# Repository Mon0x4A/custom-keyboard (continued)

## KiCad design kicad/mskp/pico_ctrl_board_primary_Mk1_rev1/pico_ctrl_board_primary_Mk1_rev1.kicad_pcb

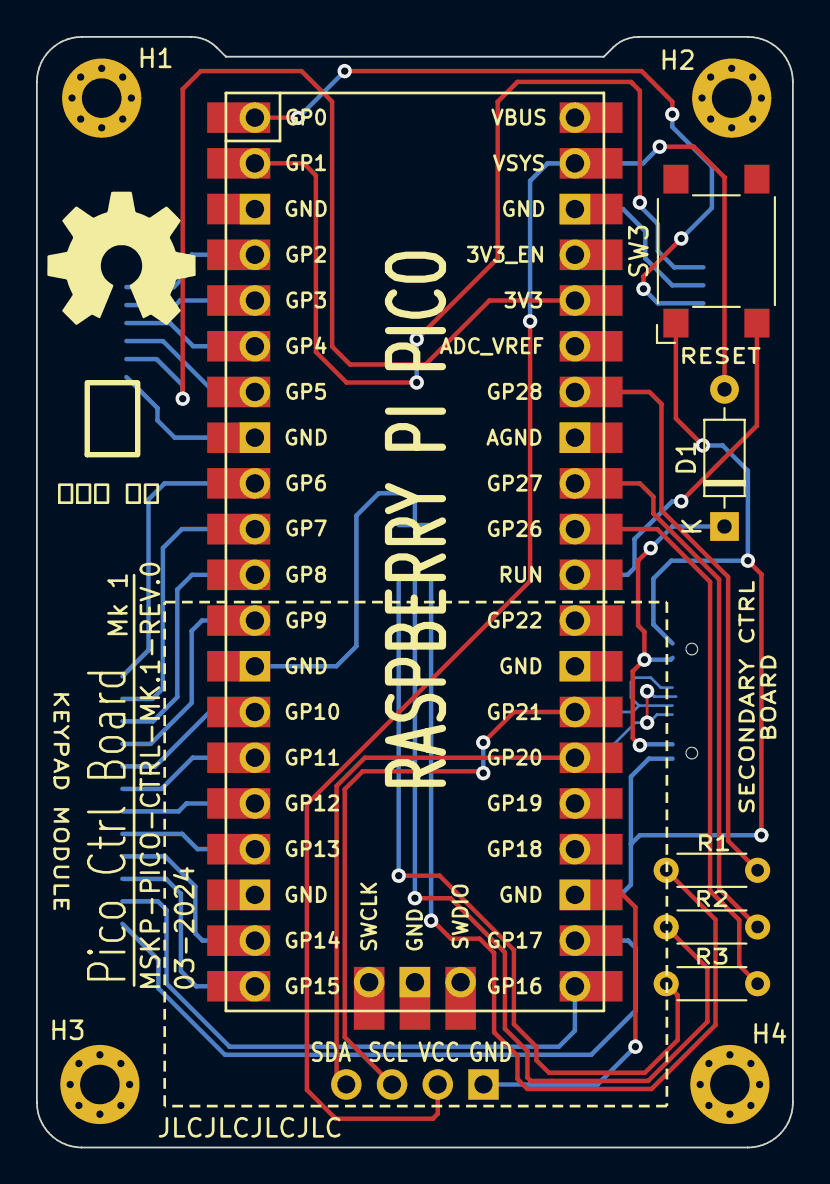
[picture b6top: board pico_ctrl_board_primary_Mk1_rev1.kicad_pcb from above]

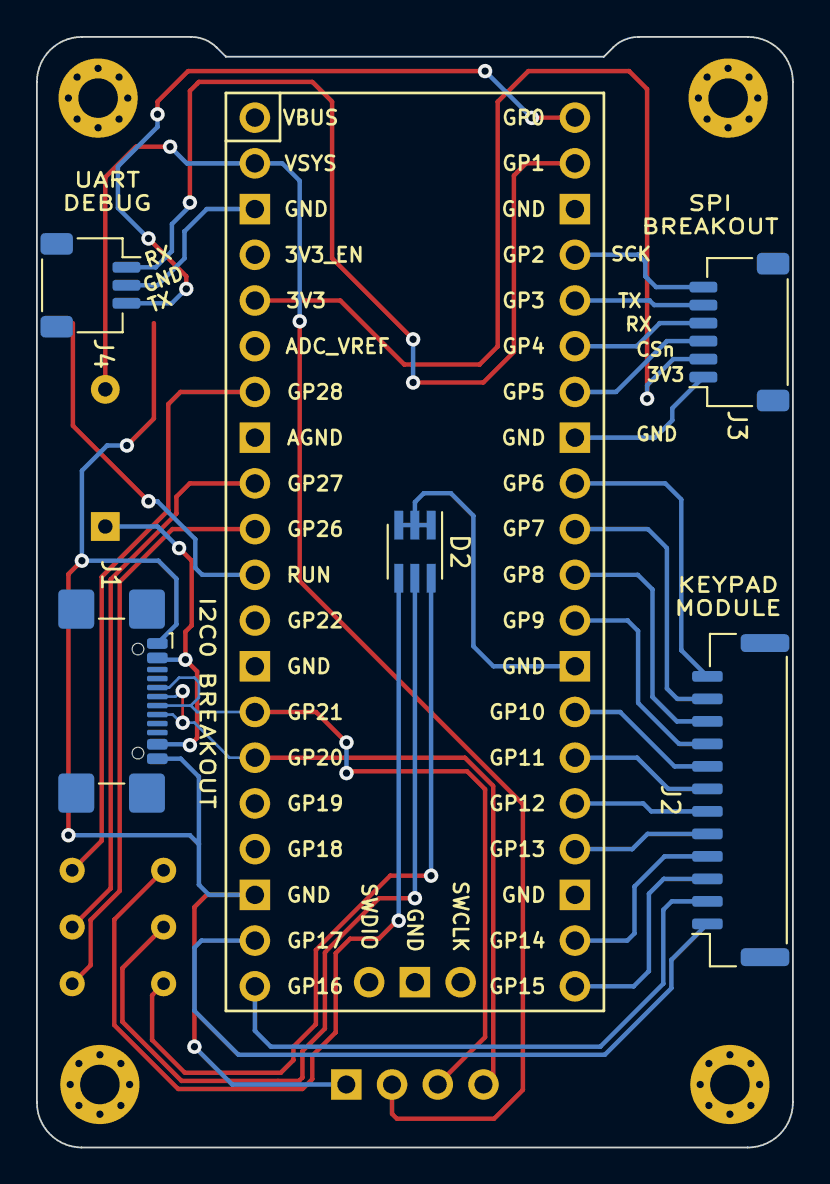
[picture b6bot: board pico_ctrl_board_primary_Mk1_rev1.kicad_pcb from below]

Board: 2 copper layers, 42.0 x 61.7 mm, 16 parts (5 on the bottom side), 34 nets.

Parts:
D1: 1N4148; D_DO-35_SOD27_P7.62mm_Horizontal
D2: ASMT-YTB7-0AA02; LED_Avago_PLCC6_3x2.8mm
H1, H2, H3, H4: MountingHole_2.2mm_M2_Pad_Via
J1: USB_C_Receptacle_USB2.0; USB_C_Receptacle_GCT_USB4110
J2: Conn_01x12_Socket; JST_GH_SM12B-GHS-TB_1x12-1MP_P1.25mm_Horizontal
J3: Conn_01x06_Socket; JST_SH_SM06B-SRSS-TB_1x06-1MP_P1.00mm_Horizontal
J4: Conn_01x03_Socket; JST_SH_SM03B-SRSS-TB_1x03-1MP_P1.00mm_Horizontal
R1, R2, R3: Resistor; R_Axial_DIN0204_L3.6mm_D1.6mm_P5.08mm_Horizontal
SW3: SW_Omron_B3FS; SW_SPST_Omron_B3FS-101xP
U1: Raspberry_Pi_Pico
U2: OLED_128x64

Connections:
GND: J4.2, U1.38 (GND)
unnamed: D1.2 (A), U1.39 (VSYS), U2.2 (VCC)
unnamed: D1.1 (K), J1.A4 (VBUS), J1.A9 (VBUS), J1.B4 (VBUS), J1.B9 (VBUS)
unnamed: D2.6 (AB), R3.1
unnamed: D2.5 (AG), R2.1
unnamed: D2.4 (AR), R1.1
unnamed: D2.1 (KB), D2.2 (KG), D2.3 (KR), U1.13 (GND)
unnamed: J2.1, U1.22 (GPIO17)
unnamed: J2.2, U1.21 (GPIO16)
unnamed: J2.3, U1.20 (GPIO15)
unnamed: J2.4, U1.19 (GPIO14)
unnamed: J2.5, U1.17 (GPIO13)
unnamed: J2.6, U1.16 (GPIO12)
unnamed: J2.7, U1.15 (GPIO11)
unnamed: J2.8, U1.14 (GPIO10)
unnamed: J2.9, U1.12 (GPIO9)
unnamed: J2.10, U1.11 (GPIO8)
unnamed: J2.11, U1.10 (GPIO7)
unnamed: J2.12, U1.9 (GPIO6)
unnamed: J3.1, U1.8 (GND)
unnamed: J3.2, U1.36 (3V3)
unnamed: J3.3, U1.7 (GPIO5)
unnamed: J3.4, U1.6 (GPIO4)
unnamed: J3.5, U1.5 (GPIO3)
unnamed: J3.6, U1.4 (GPIO2)
unnamed: J4.1, U1.2 (GPIO1)
unnamed: J4.3, U1.1 (GPIO0)
unnamed: J1.A6 (D+), J1.B6 (D+), U1.26 (GPIO20), U2.4 (SDA)
unnamed: J1.A7 (D-), J1.B7 (D-), U1.27 (GPIO21), U2.3 (SCL)
unnamed: R3.2, U1.31 (GPIO26_ADC0)
unnamed: R2.2, U1.32 (GPIO27_ADC1)
unnamed: R1.2, U1.34 (GPIO28_ADC2)
unnamed: SW3.2, U1.30 (RUN)
unnamed: J1.A1 (GND), J1.A12 (GND), J1.B1 (GND), J1.B12 (GND), SW3.1, U1.23 (GND), U2.1 (GND)

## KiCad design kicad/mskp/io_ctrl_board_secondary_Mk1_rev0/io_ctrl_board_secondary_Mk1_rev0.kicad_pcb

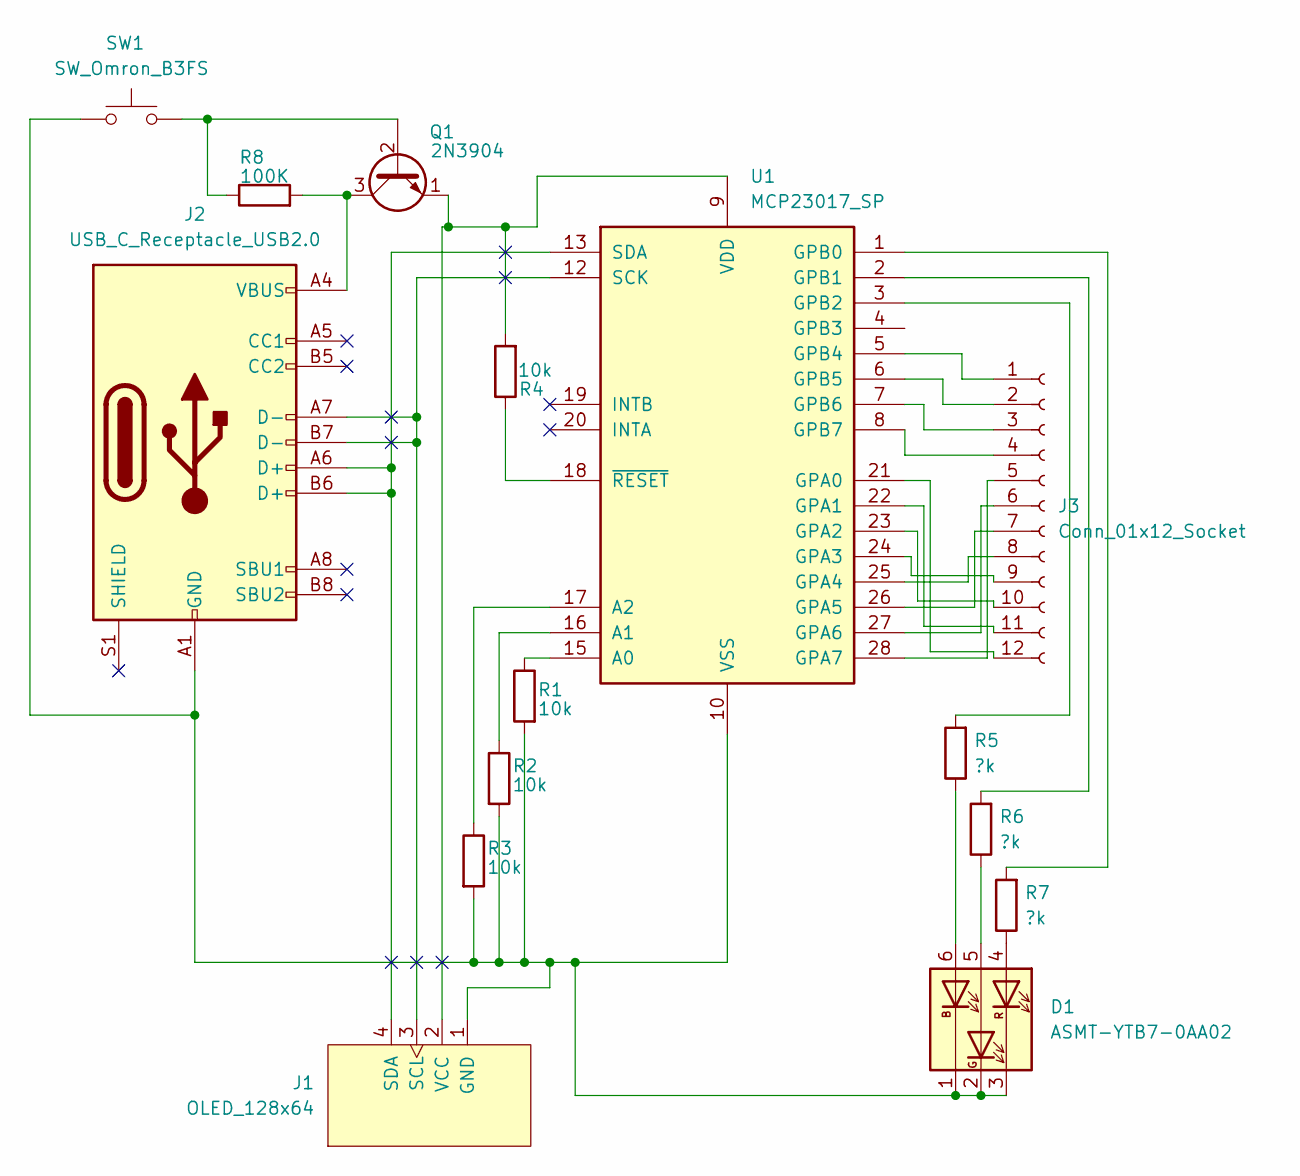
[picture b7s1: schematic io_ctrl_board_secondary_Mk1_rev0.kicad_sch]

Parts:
D1: ASMT-YTB7-0AA02; LED_Avago_PLCC6_3x2.8mm
J1: OLED_128x64
J2: USB_C_Receptacle_USB2.0; USB_C_Receptacle_GCT_USB4110
J3: Conn_01x12_Socket; JST_GH_SM12B-GHS-TB_1x12-1MP_P1.25mm_Horizontal
Q1: 2N3904; TO-92_Inline
R1, R2, R3, R4: 10k; R_Axial_DIN0204_L3.6mm_D1.6mm_P5.08mm_Horizontal
R5, R6, R7: ?k; R_Axial_DIN0204_L3.6mm_D1.6mm_P5.08mm_Horizontal
R8: 100K; R_Axial_DIN0204_L3.6mm_D1.6mm_P5.08mm_Horizontal
SW1: SW_Omron_B3FS; SW_SPST_Omron_B3FS-101xP
U1: MCP23017_SP; DIP-28_W7.62mm_Socket

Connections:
unnamed: D1.6 (AB), R5.1
unnamed: D1.5 (AG), R6.1
unnamed: D1.4 (AR), R7.1
unnamed: D1.1 (KB), D1.2 (KG), D1.3 (KR), J1.1 (GND), J2.A1 (GND), J2.A12 (GND), J2.B1 (GND), J2.B12 (GND), R1.2, R2.2, R3.2, SW1.2, U1.10 (VSS)
unnamed: J1.3 (SCL), J2.A7 (D-), J2.B7 (D-), U1.12 (SCK)
unnamed: J1.4 (SDA), J2.A6 (D+), J2.B6 (D+), U1.13 (SDA)
unnamed: J1.2 (VCC), Q1.1 (E), R4.2, U1.9 (VDD)
unnamed: J3.1, U1.5 (GPB4)
unnamed: J3.2, U1.6 (GPB5)
unnamed: J3.3, U1.7 (GPB6)
unnamed: J3.4, U1.8 (GPB7)
unnamed: J3.5, U1.28 (GPA7)
unnamed: J3.6, U1.27 (GPA6)
unnamed: J3.7, U1.26 (GPA5)
unnamed: J3.8, U1.25 (GPA4)
unnamed: J3.9, U1.24 (GPA3)
unnamed: J3.10, U1.23 (GPA2)
unnamed: J3.11, U1.22 (GPA1)
unnamed: J3.12, U1.21 (GPA0)
unnamed: Q1.2 (B), R8.1, SW1.1
unnamed: J2.A4 (VBUS), J2.A9 (VBUS), J2.B4 (VBUS), J2.B9 (VBUS), Q1.3 (C), R8.2
unnamed: R1.1, U1.15 (A0)
unnamed: R2.1, U1.16 (A1)
unnamed: R3.1, U1.17 (A2)
unnamed: R7.2, U1.1 (GPB0)
unnamed: R6.2, U1.2 (GPB1)
unnamed: R5.2, U1.3 (GPB2)
unnamed: R4.1, U1.18 (~RESET)

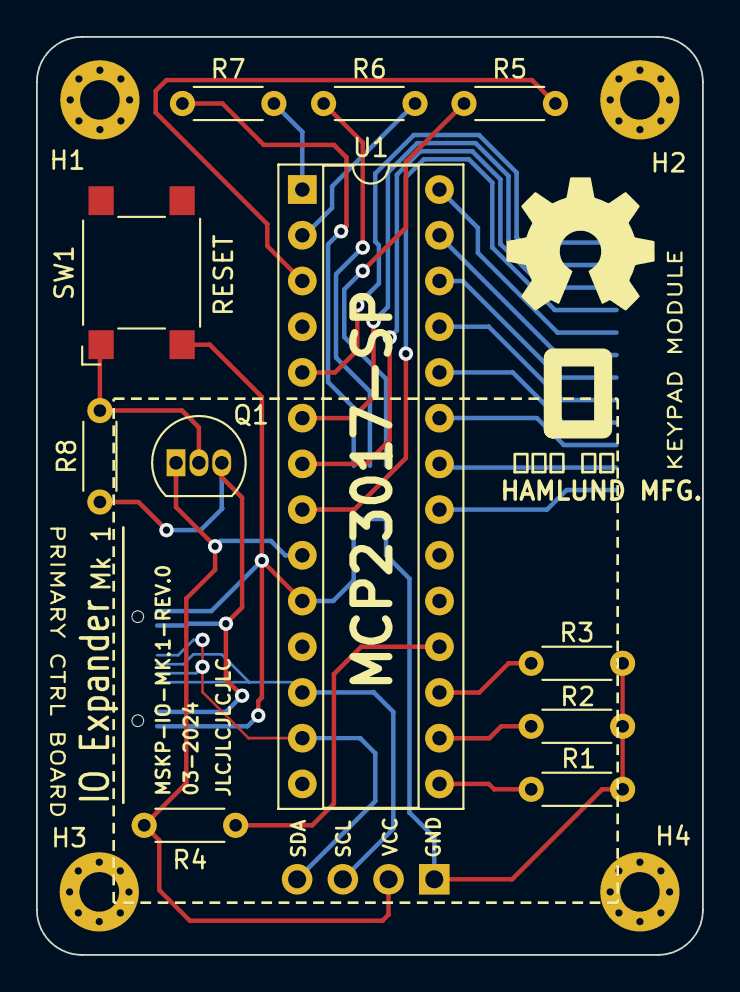
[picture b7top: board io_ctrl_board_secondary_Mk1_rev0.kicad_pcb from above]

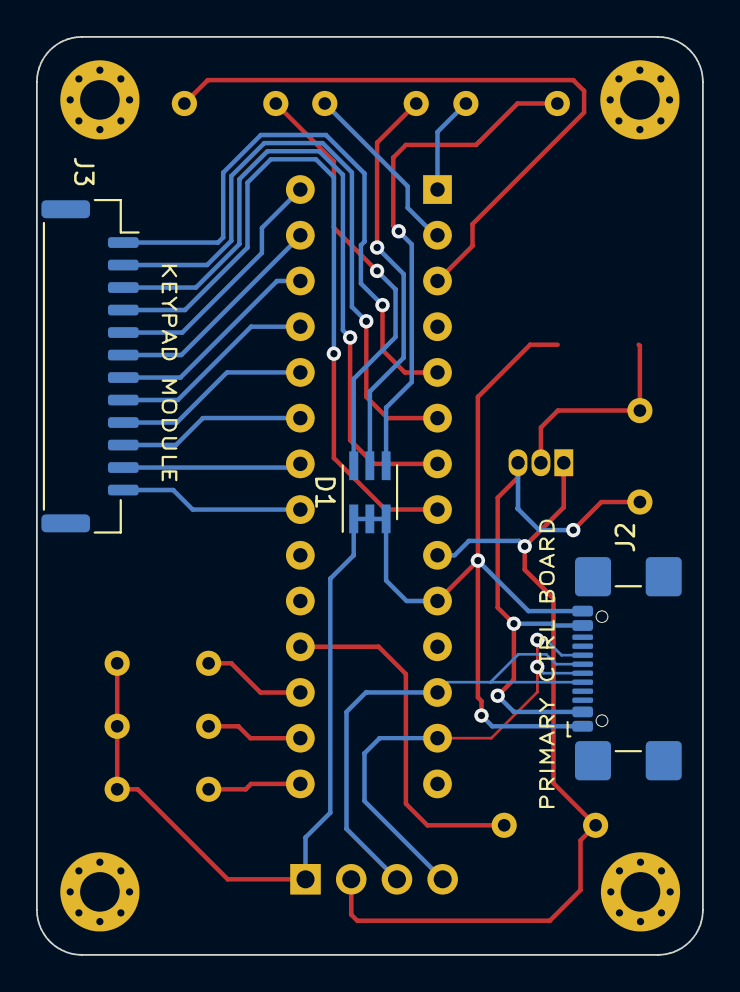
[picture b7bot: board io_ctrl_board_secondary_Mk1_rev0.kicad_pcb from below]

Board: 2 copper layers, 37.0 x 51.0 mm, 19 parts (3 on the bottom side), 28 nets.

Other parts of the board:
H1, H2, H3, H4: MountingHole_2.2mm_M2_Pad_Via

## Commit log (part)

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2023-02-13 Remove duplicate paren keys and sticky behavior for layer 2
2023-02-13 Resets the scad file render
2023-02-15 Prevents modifier from registering until after tap timeout
2023-02-15 Combines alt and OS keys into layers and cleans up unused sticky code
2023-02-15 Adds back all the sticky bool arrays for l2
2023-02-17 Adds formatting to layer keymap arrays
2023-02-17 Changes the numpad layout to be a col outwards
2023-02-18 Adds measurement print outs for keyboard housing size
2023-02-18 Adds first draft of tenting structure for mk2 keyboard
2023-02-20 Adds bolt channel cutouts to carraige beams
2023-02-20 Begins cutouts on beam structures
2023-02-22 Removes tab from the second layer due to frequent accidental strikes.
2023-02-24 Adds mod tap behavior to layer 1 modifiers and moves return key
2023-02-28 Moves modifier combo key to outer upper corners
2023-03-02 Syncs mod time out/in to avoid shifted mods being pressed
2023-03-02 Fixes off by one error in right layer 2 keymap
2023-03-03 Adds cutouts for connecting base beam and starts on tent
2023-03-04 Swaps return and tab key locations
2023-03-05 Adds housing sub module code and basic locatin outline
2023-03-06 Refactors code after relizing two variable sets was a terrible idea
2023-03-07 Adds a few more movement keybindings
2023-03-09 Adds first pass at kailh key cap top
2023-03-10 Sets up mirror call for right half rendering
2023-03-10 Fixes 'de-shift' issue on left shift
    When the Keyboard library calls write with a symbol that requires
    the shift button to print, the left shift is used in that call. As
    part of that call the (left) shift release is also called so now
    both shift button use the right shift code to avoid shift being
    disengaged while still physically held.
2023-03-11 Implements backplate risers with matching backplate bolt holes
2023-03-12 Adds straight risers to distances between corners
2023-03-15 Adds the starting values for joining the main housing and the arduino housing. Also adds the pinout diagram for the micro controller.
2023-03-16 Adds support for 1inch oled screen
2023-03-18 Oled screen adjustments and TRRS port initial draft
2023-03-19 Trims top of housing to avoid sharp corners
2023-03-25 Begins implementation of class-based Mk3 firmware
2023-03-25 Right side switch matrix functional
2023-03-26 Initial layer 0 left half with logging functions
2023-03-27 Adds the last left layer as a constant and adds it to the mapping
2023-03-27 Replaces chord method with simpler version and adds cross layer release
2023-03-28 Adds program option to enable output of keycodes over usb
2023-03-28 Fixes bug where keys were getting stuck down from layer movements in the code designed to prevent this...
2023-03-28 Removes shift tap command until i2c comms are added. Too many misfires.
2023-04-06 Adds wedge block for securing the trrs port fixture
2023-04-20 Minor work on matrix transmitter
2023-04-21 Wrist rest tweaks
2023-04-26 Changes the function keys on mk2+mk3 layouts to be more ergo
2023-04-27 Adds simple state handling for modifiers
2023-04-28 Initializes the right side transmitter
2023-04-29 Works on abstracting serial switch printing to helper
2023-04-29 Changes return key to new location which matches mk3 layout
2023-05-02 Begins first testing drafts of trackball housing
2023-05-04 Reworks keyboard state objects to global scope to avoid crashes when dereferencing more than the board can handle
2023-05-05 Moves Wire logic outside of state provider to global context to prevent crashes. Uses function pointer to preserve structure.
2023-05-06 Moves layer objects to global variables
2023-05-06 Removes all unused code
2023-05-08 Fixes bug where right shift release was being fired undesireably and comments out lots of logging code
2023-05-13 Deletes unused code and optimizes/fixes matrix printing
2023-05-13 Moves chord action variable to keyboard state container
    This commit changes the location of the chord performed
    flag to the keyboard state container to support chords
    that utilize both halves of the keyboard.
2023-05-17 Updates two const arrays to match their references
    This appeared as a complier error in the v2 version
    of the arduino IDE.
2023-05-21 Fixes indents and begins making space for pico
2023-05-31 Adds pico documentation to resources
2023-06-04 Fixes the floating pin state on the Pico code
    This commit changes the way switch state is measured by
    setting the column pins to always be INPUT_PULLUP. The
    method of 'just in time' setting the pinMode() was causing
    the pin values to float irratically.
2023-06-04 Implements housing sizing for pico
2023-06-10 Tweaks the pico housing top for first printing
2023-06-21 Adds changes to pin connections in mk4
2023-06-21 Adds initial commit of pico sdk firmware
2023-06-22 Adds required edits to initialize tinyusb
2023-06-23 More code cleanup and formatting changes
2023-06-23 Adds structure comments to c files
2023-06-25 Continues to flesh out project structure
2023-06-25 Adds the logic to poll switch states and printf it
2023-06-26 Makes all source files include their own headers
2023-06-28 Removes typedef from all structs for more readability
2023-06-28 Finishes fleshing out key state module
2023-07-01 Implements basic press/release handling
2023-07-01 Fixes to get basic layer 0 keycodes sending!
2023-07-02 Sets up initial pass at peripheral side logic
2023-07-03 Adds basic test code to transmit over I2C
2023-07-04 Adds logic for basic single tap handling
2023-07-06 Begins work on mk5 unibody design
2023-07-07 Beginning to build up bridge section
2023-07-07 Adds grid decorations, punches and screen cover to bridge
2023-07-08 Adds allowances for usbc breakout passthrough
2023-07-12 Adds center bridge cutout and corrects 'enter' HID keycode
2023-07-14 Adds config mode for unibody keyboard layout
2023-07-15 Adds pin config for unibody keyboard
2023-07-15 Adds dedicated keyboard state module and begins QoL key features
2023-07-16 Left side control code is causing issues for tap chords. Temp fix.
2023-07-18 Code clean and refactor comments
2023-07-27 Breaks out sdd1306 constants and buffer ops to new files
2023-07-29 Updates the usbc clamp design with increased surface area
2023-07-29 Begins display state managment and namespace
2023-08-03 Refactors kailh keycap out into its own file
2023-08-03 Refactors all display classes into relevant directory
2023-08-09 Begins config refactor and adds test macro types
2023-08-13 Begins experimentation with simple IO expander instructions
2023-08-20 Begins mk6 scad revisions
2023-08-22 Adds struct for delay hold callback parameters
2023-08-24 Majority of work to get the tap/hold layout working
2023-08-24 Condenses layer array value fetching logic
2023-08-24 Snapshots modifier state on tap event down
2023-08-26 Adjusts kailh cap tolerances and mx backplate
2023-08-30 Begins work on io expander implementation
2023-09-05 Refactors press helper methods for QoL
2023-09-07 Condenses keymap declaration with structs
2023-09-08 Fixes bug in delay params malloc
2023-09-09 Switches away from side logic, condenses keymap code
2023-10-14 Adds first draft of qlp-22 kicad project
2023-10-17 Adds row traces and comments for additional components
2023-10-18 Adds gitignore
2023-10-19 Revises left hand centering back to original location
2023-10-21 Finishes revisions to f.Cu on qlp-22
2023-10-21 Creates initial pcb edge outline for qlp-22
2023-10-22 Updates gitignore to include lock files
2023-10-22 Adds front qlp-22 silkscreen for all switches and diodes
2023-11-03 Corrects I2C variable usage in display code
2023-11-05 Implements basic sticky layering for qlp
2023-11-06 Adjusts the time alloted for momentary key presses
2023-11-16 Ensures that modifiers don't complete chords
2023-11-17 Resizes the kailh choc cap to more standard size
2023-11-22 Begins work on qlp-22_Mk1_rev1 ergo positions
2023-11-24 Places initial mounting holes
2023-11-26 Moves microcontroller config to main config file
2023-11-30 Removes fCu dimensions, adds silkscreen to qlp-22_Mk1_rev1
2023-12-04 Adds more row wiring to right side
2023-12-09 Adds majority of column hookups for qlp-22_Mk1_rev1
2024-01-15 Prevents setting of keyboard chord state on null keycode
2024-01-17 Finishes labeling for qlp-22_Mk1_rev1
2024-01-19 Adds left half edgecuts for seok-38_Mk1_rev0
2024-01-21 Adjusts qlp-22_Mk1_rev1 tracks around mounting holes
2024-01-22 Adds column wiring to seok-38_Mk1_rev0
2024-01-24 Completes column hookups for seok-38_Mk1_rev0
2024-01-25 Add final silkscreen labelling to seok-38_Mk1_rev0
2024-01-29 Final silkscreen and DRC tweaks before manufacturing
2024-02-04 Updates the poll interval rate
2024-02-09 Adds keymap for qlp_22_rev1
2024-02-13 Adds user layer 1 for mounting hole highlights on qlp_22_rev1
2024-02-18 Adds user layer highlights for case in seok-38_Mk1_rev0
2024-02-22 Begins schematics for PCB-based modular keyboard design
2024-02-24 Removes tab from main layer and adds another repeat key
2024-02-26 temp
2024-02-29 Adds wiring for qlp-22_mx_hs_keypad_L_Mk1_rev0
2024-02-29 Adds slightly shorter press for system mods
2024-03-01 Adds the initial revision of seok_38_rev0_keymap_m
2024-03-03 Gets seok config working and adds display enabled toggle
2024-03-04 Adds qlp-22_mx_hs_keypad_R_Mk1_rev0 with initial layout
2024-03-04 Adds work on io_ctrl_board_secondary_Mk1_rev0 pcb
2024-03-08 Partial work on mskp part silkscreens
2024-03-09 Adds wiring for io_ctrl_board_secondary_Mk1_rev0
2024-03-10 Polishes silkscreen on io_ctrl_board_secondary_Mk1_rev0
2024-03-11 Cleans up unneeded files and adds more silkscreen tidy
2024-03-14 Finalizes mskp pcbs before first run
2024-03-15 Adds user layer for bolt risers on two PCBs
2024-03-18 Updates the pico pcb riser holes to play nicer with extruding
2024-03-24 Get peripheral code working with a mcp23017 io expander
2024-04-02 Begins work on seok-42_mx_keypad_L_Mk1_rev0
2024-04-05 Initial work on seok-42_mx_keypad_L_Mk1_rev0 layout
2024-04-11 Minor keypad design update ideas
2024-04-11 Adds backplate designs for mskp qlp case
2024-04-23 Add diodes positions to seok-42_mx_keypad_L_Mk1_rev0
2024-06-09 Add timeout for i2c write instruction call
    This commit attempts to solve a issue where the
    i2c_write_blocking method would hang indefinitely
    in the event that a write instruction was not
    acknowledged, thus never receives a return. The
    change to i2c_write_blocking_until, timeout and
    retry seems to help resolve this issue.
2024-06-09 Moves peripheral key handler to correct directory
2024-06-09 Todo tidying
2024-06-20 Sync switch state modules
2024-06-22 Comment cleanup
2024-07-28 Adds sleep fix for 2 row key misfires. Correct method params.
    This commit adds a fix for 2 row matrices not having
    enough time to bring the pin state LOW before testing
    another matrix location. Additionally, fixes for a pin
    lookup method in the peripheral state code not being
    passed params. Other changes are for variable name style
    refactors.
2024-08-30 Adds first draft of usbc switch board schematic
2024-09-07 Adds first drafts of adc mouse and io expander mk2
2024-09-16 Initital footprint assignment to all control boards
2024-09-21 Begins rough PCB part grouping for all control board revisions
2024-09-23 Refining PCB outlines for pico and io control boards
2024-09-30 Initial layout work on pico_ctrl_board_primary_Mk2_rev0 PCB
2024-10-07 Initial PCB layout for usbc_switch_board_Mk1_rev0
2024-10-19 Change paginated layout to Colemak-DH
2024-10-25 Adds initial PCB layout for seok-42_mx_keypad_Mk1_rev0
2024-10-28 Adds silkscreen for pico_ctrl_board_primary_Mk2_rev0
2024-11-02 Adds silkscreen to usbc_switch_board_Mk1_rev0 PCB
2024-11-04 Adds the silkscreen for lpk20_mx_keypad_L_Mk1_rev0 PCB
2024-11-04 Adds silkscreen for seok-42_mx_keypad_L_Mk1_rev0 PCB
2024-11-22 Adds initial case and backplate work for lpk20_mk1
2024-12-22 Adds new mskp lpk20 test cases
2024-12-22 Adds initial lpk20 key map logic
2024-12-23 Add initial mounting puck model
2025-01-09 Breaks out mcp23017 control code into its own files
2025-02-13 Removes unused code and updates layer volatility
2025-04-05 Corrects unused loop variable
2025-04-05 Adds ctrl to base of esc/enter
2025-06-09 Adds right and left keycode variants of the layer mods
2025-09-10 Add keymap for handwire_dactyl_lpk20
